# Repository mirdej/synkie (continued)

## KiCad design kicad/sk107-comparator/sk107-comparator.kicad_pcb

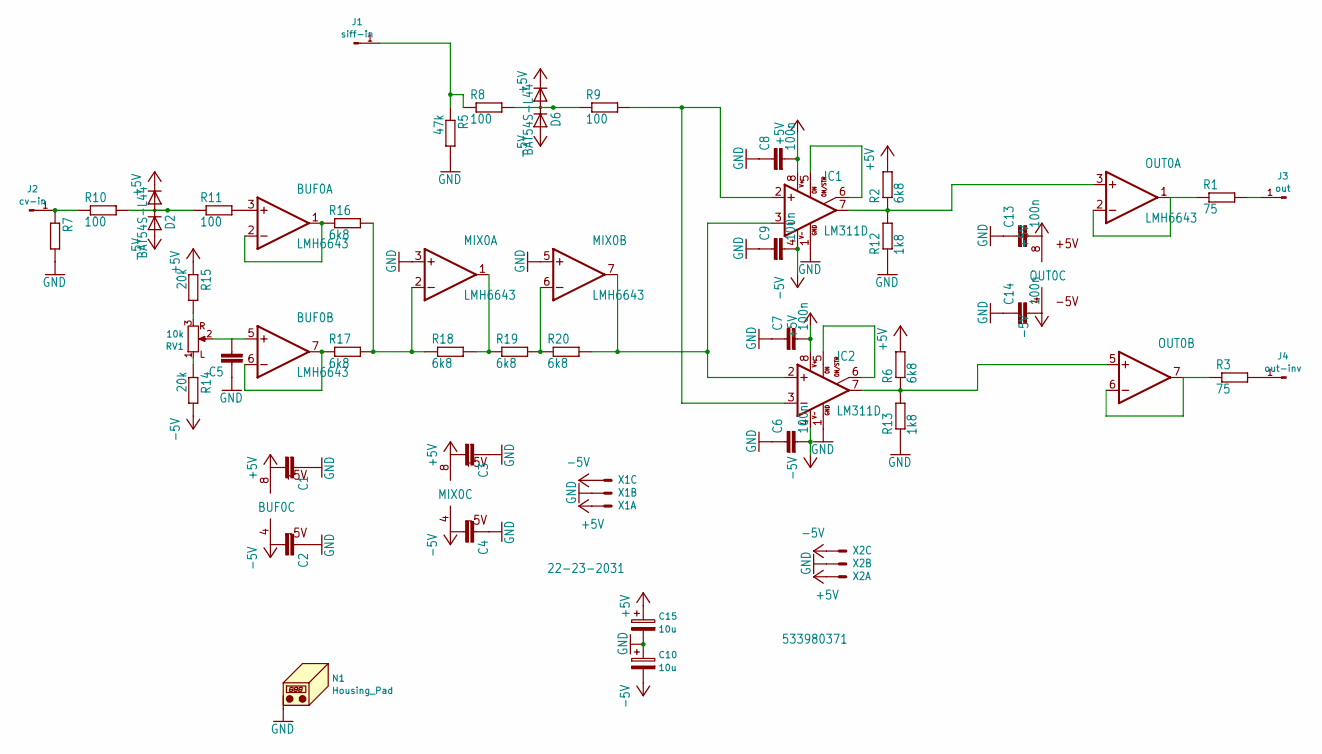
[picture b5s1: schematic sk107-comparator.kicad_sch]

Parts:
BUF0: LMH6643; VSSOP-8_3x3mm_P0.65mm; LCSC C478382
C1, C2, C3, C4, C5, C6, C7, C8, C9, C13, C14: 100n; C_0603_1608Metric_Pad1.05x0.95mm_HandSolder; LCSC C14663
C10, C15: 10u; C_1206_3216Metric_Pad1.42x1.75mm_HandSolder; LCSC C13585
D2, D6: BAT54S-L44; SOT-23; LCSC C8592
IC1, IC2: LM311D; SOIC-8_3.9x4.9mm_P1.27mm; LCSC C12597
J1: siff-in; Banana2mm-Löthülse
J2: cv-in; Banana2mm-Löthülse
J3: out; Banana2mm-Löthülse
J4: out-inv; Banana2mm-Löthülse
MIX0: LMH6643; VSSOP-8_3x3mm_P0.65mm; LCSC C478382
N1: Housing_Pad; Frontplate_20mm
OUT0: LMH6643; VSSOP-8_3x3mm_P0.65mm; LCSC C478382
R1, R3: 75; R_0603_1608Metric; LCSC C4275
R2, R6, R16, R17, R18, R19, R20: 6k8; R_0603_1608Metric; LCSC C23212
R5, R7: 47k; R_0603_1608Metric; LCSC C25819
R8, R9, R10, R11: 100; R_0603_1608Metric; LCSC C22775
R12, R13: 1k8; R_0603_1608Metric; LCSC C4177
R14, R15: 20k; R_0603_1608Metric; LCSC C4184
RV1: 10k; Alps_RK097_Frontplate
X1: 22-23-2031; Molex_KK-254_AE-6410-03A_1x03_P2.54mm_Vertical_SMD
X2: 533980371; Molex_PicoBlade_53398-0371_1x03-1MP_P1.25mm_Vertical; LCSC C293633

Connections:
+5V: BUF0.8 (+5V), C1.2, C3.2, C7.2, C8.2, C13.2, C15.1, D2.2 (C), D6.2 (C), IC1.8 (V+), IC2.8 (V+), MIX0.8 (+5V), OUT0.8 (+5V), R2.2, R6.2, R15.1, X1.1 (S), X2.1 (S)
-5V: BUF0.4 (-5V), C2.2, C4.2, C6.2, C9.2, C10.2, C14.2, D2.1 (A), D6.1 (A), IC1.4 (V-), IC2.4 (V-), MIX0.4 (-5V), OUT0.4 (-5V), R14.2, X1.3 (S), X2.3 (S)
GND: C1.1, C2.1, C3.1, C4.1, C5.1, C6.1, C7.1, C8.1, C9.1, C10.1, C13.1, C14.1, C15.2, IC1.1 (GND), IC2.1 (GND), MIX0.3 (+IN), MIX0.5 (+IN), N1.1 (PAD_1), R5.2, R7.2, R12.1, R13.1, X1.2 (S), X2.2 (S)
unnamed: BUF0.3 (+IN), R11.2
unnamed: BUF0.1 (OUT), BUF0.2 (-IN), R16.1
unnamed: BUF0.5 (+IN), C5.2, RV1.2
unnamed: BUF0.6 (-IN), BUF0.7 (OUT), R17.1
unnamed: D2.3 (AC), R10.2, R11.1
unnamed: D6.3 (AC), R8.2, R9.1
unnamed: IC1.2 (+IN), IC2.3 (-IN), R9.2
unnamed: IC1.3 (-IN), IC2.2 (+IN), MIX0.7 (OUT), R20.2
unnamed: IC1.5 (ON), IC1.6 (ON/STR)
unnamed: IC1.7 (OUT), OUT0.3 (+IN), R2.1, R12.2
unnamed: IC2.5 (ON), IC2.6 (ON/STR)
unnamed: IC2.7 (OUT), OUT0.5 (+IN), R6.1, R13.2
unnamed: J1.1 (Pin_1_1), R5.1, R8.1
unnamed: J2.1 (Pin_1_1), R7.1, R10.1
unnamed: J3.1 (Pin_1_1), R1.2
unnamed: J4.1 (Pin_1_1), R3.2
unnamed: MIX0.2 (-IN), R16.2, R17.2, R18.1
unnamed: MIX0.1 (OUT), R18.2, R19.1
unnamed: MIX0.6 (-IN), R19.2, R20.1
unnamed: OUT0.1 (OUT), OUT0.2 (-IN), R1.1
unnamed: OUT0.6 (-IN), OUT0.7 (OUT), R3.1
unnamed: R15.2, RV1.3
unnamed: R14.1, RV1.1 (L)

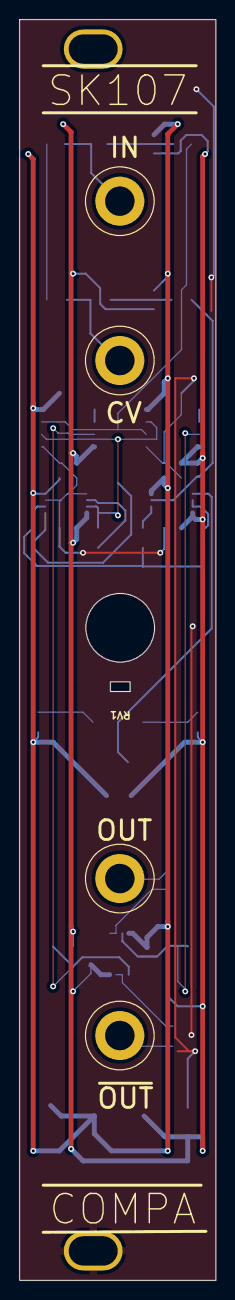
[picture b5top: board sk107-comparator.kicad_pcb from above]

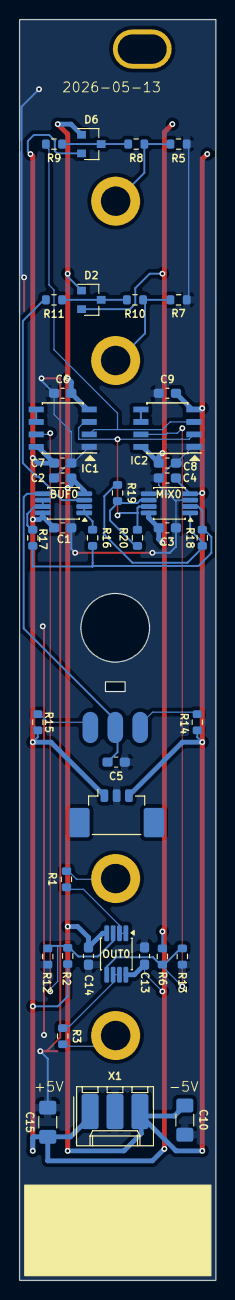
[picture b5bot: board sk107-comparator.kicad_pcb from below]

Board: 2 copper layers, 20.0 x 128.5 mm, 47 parts (41 on the bottom side), 26 nets.

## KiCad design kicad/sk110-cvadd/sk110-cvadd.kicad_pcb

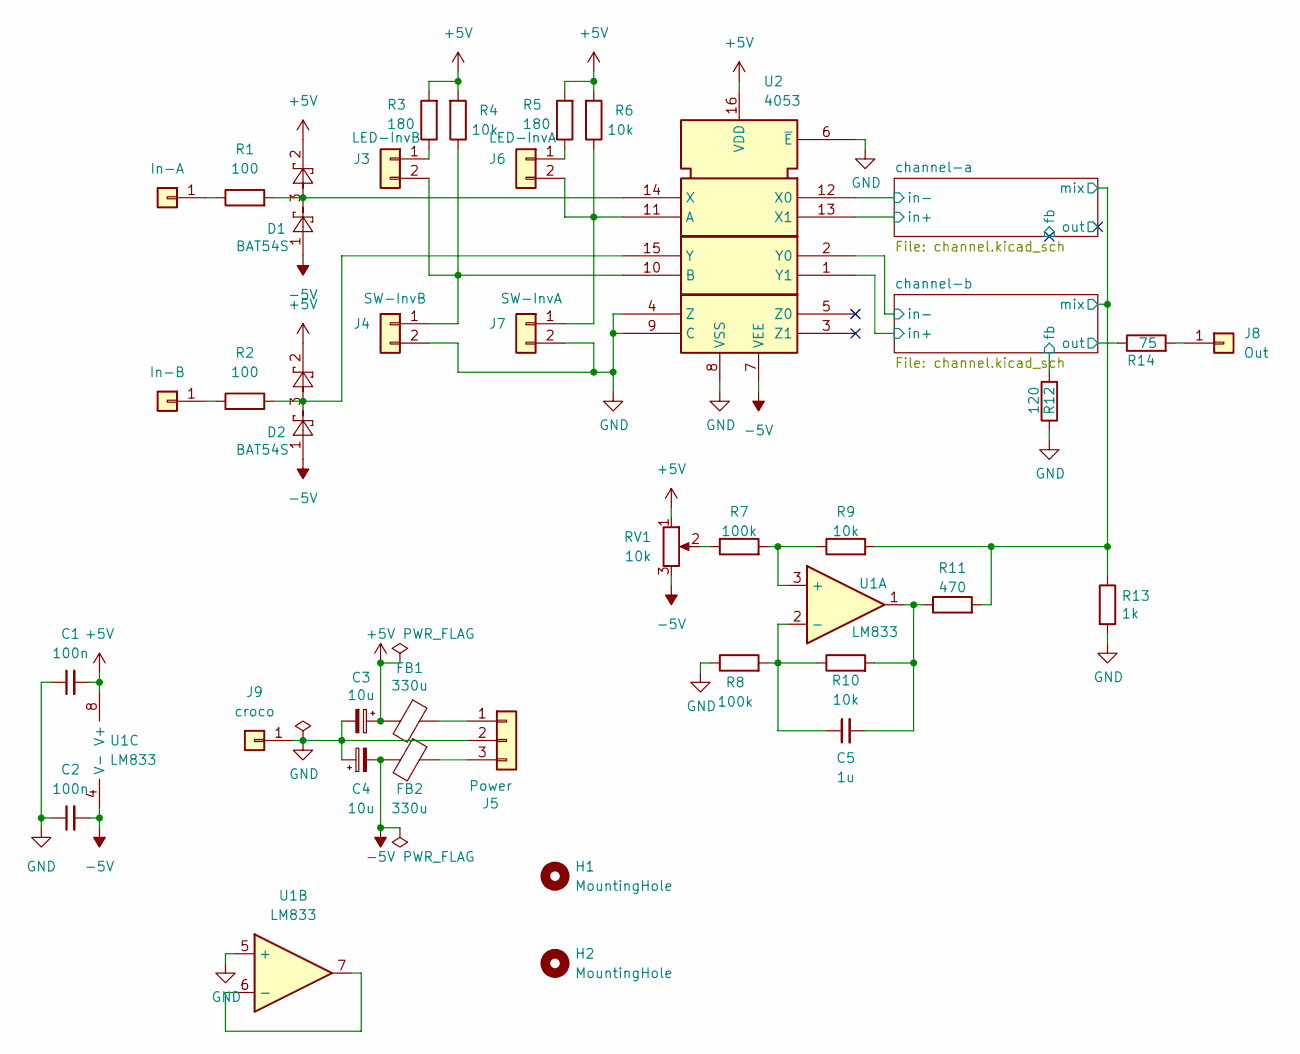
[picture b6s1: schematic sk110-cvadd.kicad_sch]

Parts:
C1, C2: 100n; C_0603_1608Metric_Pad1.05x0.95mm_HandSolder
C3, C4: 10u; C_0805_2012Metric_Pad1.15x1.40mm_HandSolder
C5: 1u; C_0603_1608Metric_Pad1.05x0.95mm_HandSolder
D1, D2: BAT54S; SOT-23
FB1, FB2: 330u; L_0805_2012Metric_Pad1.15x1.40mm_HandSolder
H1, H2: MountingHole; MountingHole_3.2mm_M3_DIN965
J1: In-A; Solderpad-SYNKIEPAD-2mm
J2: In-B; Solderpad-SYNKIEPAD-2mm
J3: LED-InvB; Molex_KK-254_AE-6410-02A_1x02_P2.54mm_Vertical
J4: SW-InvB; Molex_KK-254_AE-6410-02A_1x02_P2.54mm_Vertical
J5: Power; Molex_KK-254_AE-6410-03A_1x03_P2.54mm_Vertical
J6: LED-InvA; Molex_KK-254_AE-6410-02A_1x02_P2.54mm_Vertical
J7: SW-InvA; Molex_KK-254_AE-6410-02A_1x02_P2.54mm_Vertical
J8: Out; Solderpad-SYNKIEPAD-2mm
J9: croco; CrocodileGroundPad
R1, R2: 100; R_0805_2012Metric_Pad1.15x1.40mm_HandSolder
R3, R5: 180; R_0805_2012Metric_Pad1.15x1.40mm_HandSolder
R4, R6, R9, R10: 10k; R_0805_2012Metric_Pad1.15x1.40mm_HandSolder
R7, R8: 100k; R_0805_2012Metric_Pad1.15x1.40mm_HandSolder
R11: 470; R_0805_2012Metric_Pad1.15x1.40mm_HandSolder
R12: 120; R_0805_2012Metric_Pad1.15x1.40mm_HandSolder
R13: 1k; R_0805_2012Metric_Pad1.15x1.40mm_HandSolder
R14: 75; R_0805_2012Metric_Pad1.15x1.40mm_HandSolder
RV1: 10k; Potentiometer_Alps_RK09K_Single_Horizontal
U1: LM833; SOIC-8_3.9x4.9mm_P1.27mm
U2: 4053; SOIC-16_3.9x9.9mm_P1.27mm

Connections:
+5V: C1.2, C3.1, D1.2, D2.2, FB1.2, R3.2, R4.2, R5.2, R6.2, RV1.1, U1.8 (V+), U2.16 (VDD); also elsewhere on the board
-5V: C2.2, C4.2, D1.1, D2.1, FB2.2, RV1.3, U1.4 (V-), U2.7 (VEE); also elsewhere on the board
/channel-a/in+: U2.13 (X1); also elsewhere on the board
/channel-a/in-: U2.12 (X0); also elsewhere on the board
/channel-a/mix: R9.2, R11.2, R13.1; also elsewhere on the board
/channel-b/fb: R12.2; also elsewhere on the board
/channel-b/in+: U2.1 (Y1); also elsewhere on the board
/channel-b/in-: U2.2 (Y0); also elsewhere on the board
/channel-b/out: R14.1; also elsewhere on the board
GND: C1.1, C2.1, C3.2, C4.1, J4.2, J5.2, J7.2, J9.1, R8.1, R12.1, R13.2, U1.5 (+), U2.4 (Z), U2.6 (~E), U2.8 (VSS), U2.9 (C); also elsewhere on the board
unnamed: C5.2, R10.2, R11.1, U1.1
unnamed: J1.1, R1.1
unnamed: J2.1, R2.1
unnamed: J3.1, R3.1
unnamed: J3.2, J4.1, R4.1, U2.10 (B)
unnamed: FB1.1, J5.1
unnamed: FB2.1, J5.3
unnamed: J6.1, R5.1
unnamed: J6.2, J7.1, R6.1, U2.11 (A)
unnamed: J8.1, R14.2
unnamed: R7.1, RV1.2
unnamed: R7.2, R9.1, U1.3 (+)
unnamed: C5.1, R8.2, R10.1, U1.2 (-)
unnamed: U1.6 (-), U1.7
unnamed: D1.3, R1.2, U2.14 (X)
unnamed: D2.3, R2.2, U2.15 (Y)

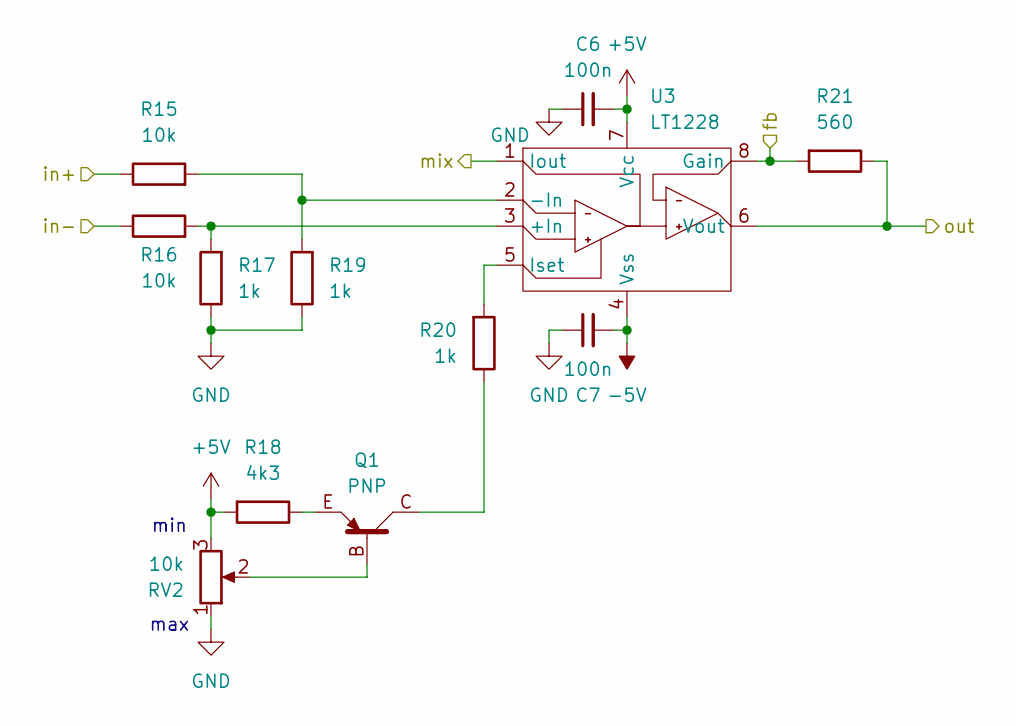
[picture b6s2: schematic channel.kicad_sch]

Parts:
C6, C7: 100n; C_0603_1608Metric_Pad1.05x0.95mm_HandSolder
Q1: PNP; SOT-23_BEC
R15, R16: 10k; R_0805_2012Metric_Pad1.15x1.40mm_HandSolder
R17, R19, R20: 1k; R_0805_2012Metric_Pad1.15x1.40mm_HandSolder
R18: 4k3; R_0805_2012Metric_Pad1.15x1.40mm_HandSolder
R21: 560; R_0805_2012Metric_Pad1.15x1.40mm_HandSolder
RV2: 10k; Potentiometer_Alps_RK09K_Single_Horizontal
U3: LT1228; SOIC-8_3.9x4.9mm_P1.27mm

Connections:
+5V: C6.2, R18.2, RV2.3, U3.7 (Vcc); also elsewhere on the board
-5V: C7.2, U3.4 (Vss); also elsewhere on the board
/channel-a/fb: R21.2, U3.8 (Gain)
/channel-a/in+: R15.1; also elsewhere on the board
/channel-a/in-: R16.1; also elsewhere on the board
/channel-a/mix: U3.1 (Iout); also elsewhere on the board
/channel-a/out: R21.1, U3.6 (Vout)
GND: C6.1, C7.1, R17.1, R19.1, RV2.1; also elsewhere on the board
unnamed: Q1.B, RV2.2
unnamed: Q1.C, R20.1
unnamed: Q1.E, R18.1
unnamed: R16.2, R17.2, U3.3 (+In)
unnamed: R15.2, R19.2, U3.2 (-In)
unnamed: R20.2, U3.5 (Iset)

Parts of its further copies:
C8, C9: 100n; C_0603_1608Metric_Pad1.05x0.95mm_HandSolder
Q2: PNP; SOT-23_BEC
R22, R23: 10k; R_0805_2012Metric_Pad1.15x1.40mm_HandSolder
R24, R26, R27: 1k; R_0805_2012Metric_Pad1.15x1.40mm_HandSolder
R25: 4k3; R_0805_2012Metric_Pad1.15x1.40mm_HandSolder
R28: 560; R_0805_2012Metric_Pad1.15x1.40mm_HandSolder
RV3: 10k; Potentiometer_Alps_RK09K_Single_Horizontal
U4: LT1228; SOIC-8_3.9x4.9mm_P1.27mm

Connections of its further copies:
+5V: C8.2, R25.2, RV3.3, U4.7 (Vcc); also elsewhere on the board
-5V: C9.2, U4.4 (Vss); also elsewhere on the board
/channel-a/mix: U4.1 (Iout); also elsewhere on the board
/channel-b/fb: R28.2, U4.8 (Gain); also elsewhere on the board
/channel-b/in+: R22.1; also elsewhere on the board
/channel-b/in-: R23.1; also elsewhere on the board
/channel-b/out: R28.1, U4.6 (Vout); also elsewhere on the board
GND: C8.1, C9.1, R24.1, R26.1, RV3.1; also elsewhere on the board
unnamed: Q2.B, RV3.2
unnamed: Q2.C, R27.1
unnamed: Q2.E, R25.1
unnamed: R23.2, R24.2, U4.3 (+In)
unnamed: R22.2, R26.2, U4.2 (-In)
unnamed: R27.2, U4.5 (Iset)

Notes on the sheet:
max
min

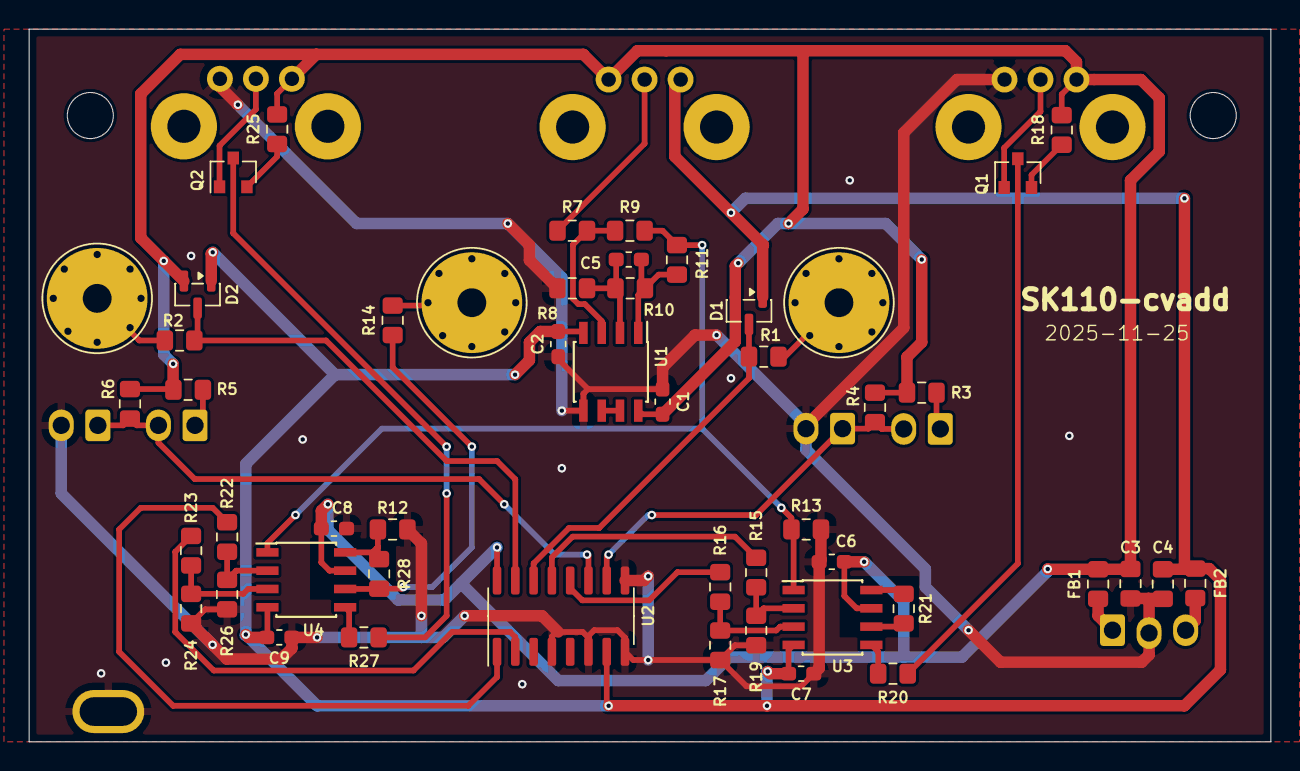
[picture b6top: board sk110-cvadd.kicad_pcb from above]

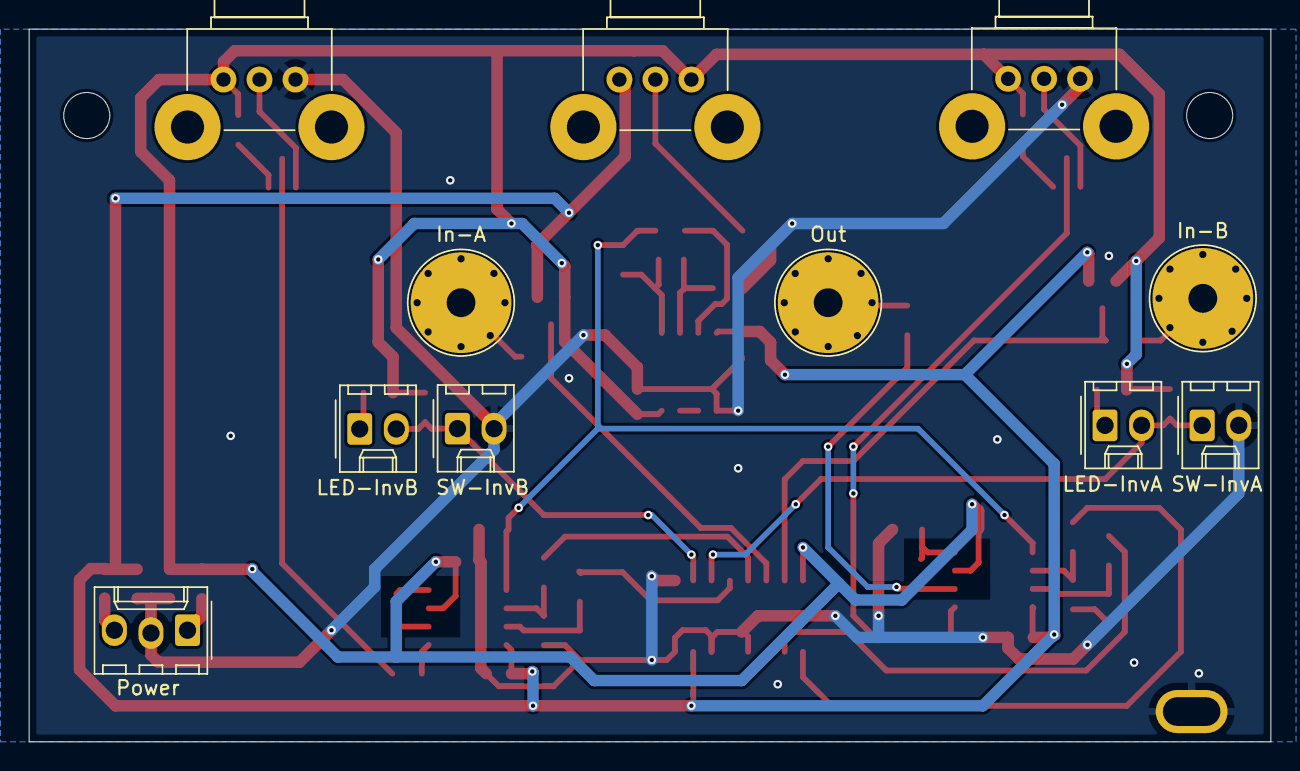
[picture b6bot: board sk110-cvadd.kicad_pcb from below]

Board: 2 copper layers, 86.2 x 49.5 mm, 61 parts (8 on the bottom side), 40 nets.

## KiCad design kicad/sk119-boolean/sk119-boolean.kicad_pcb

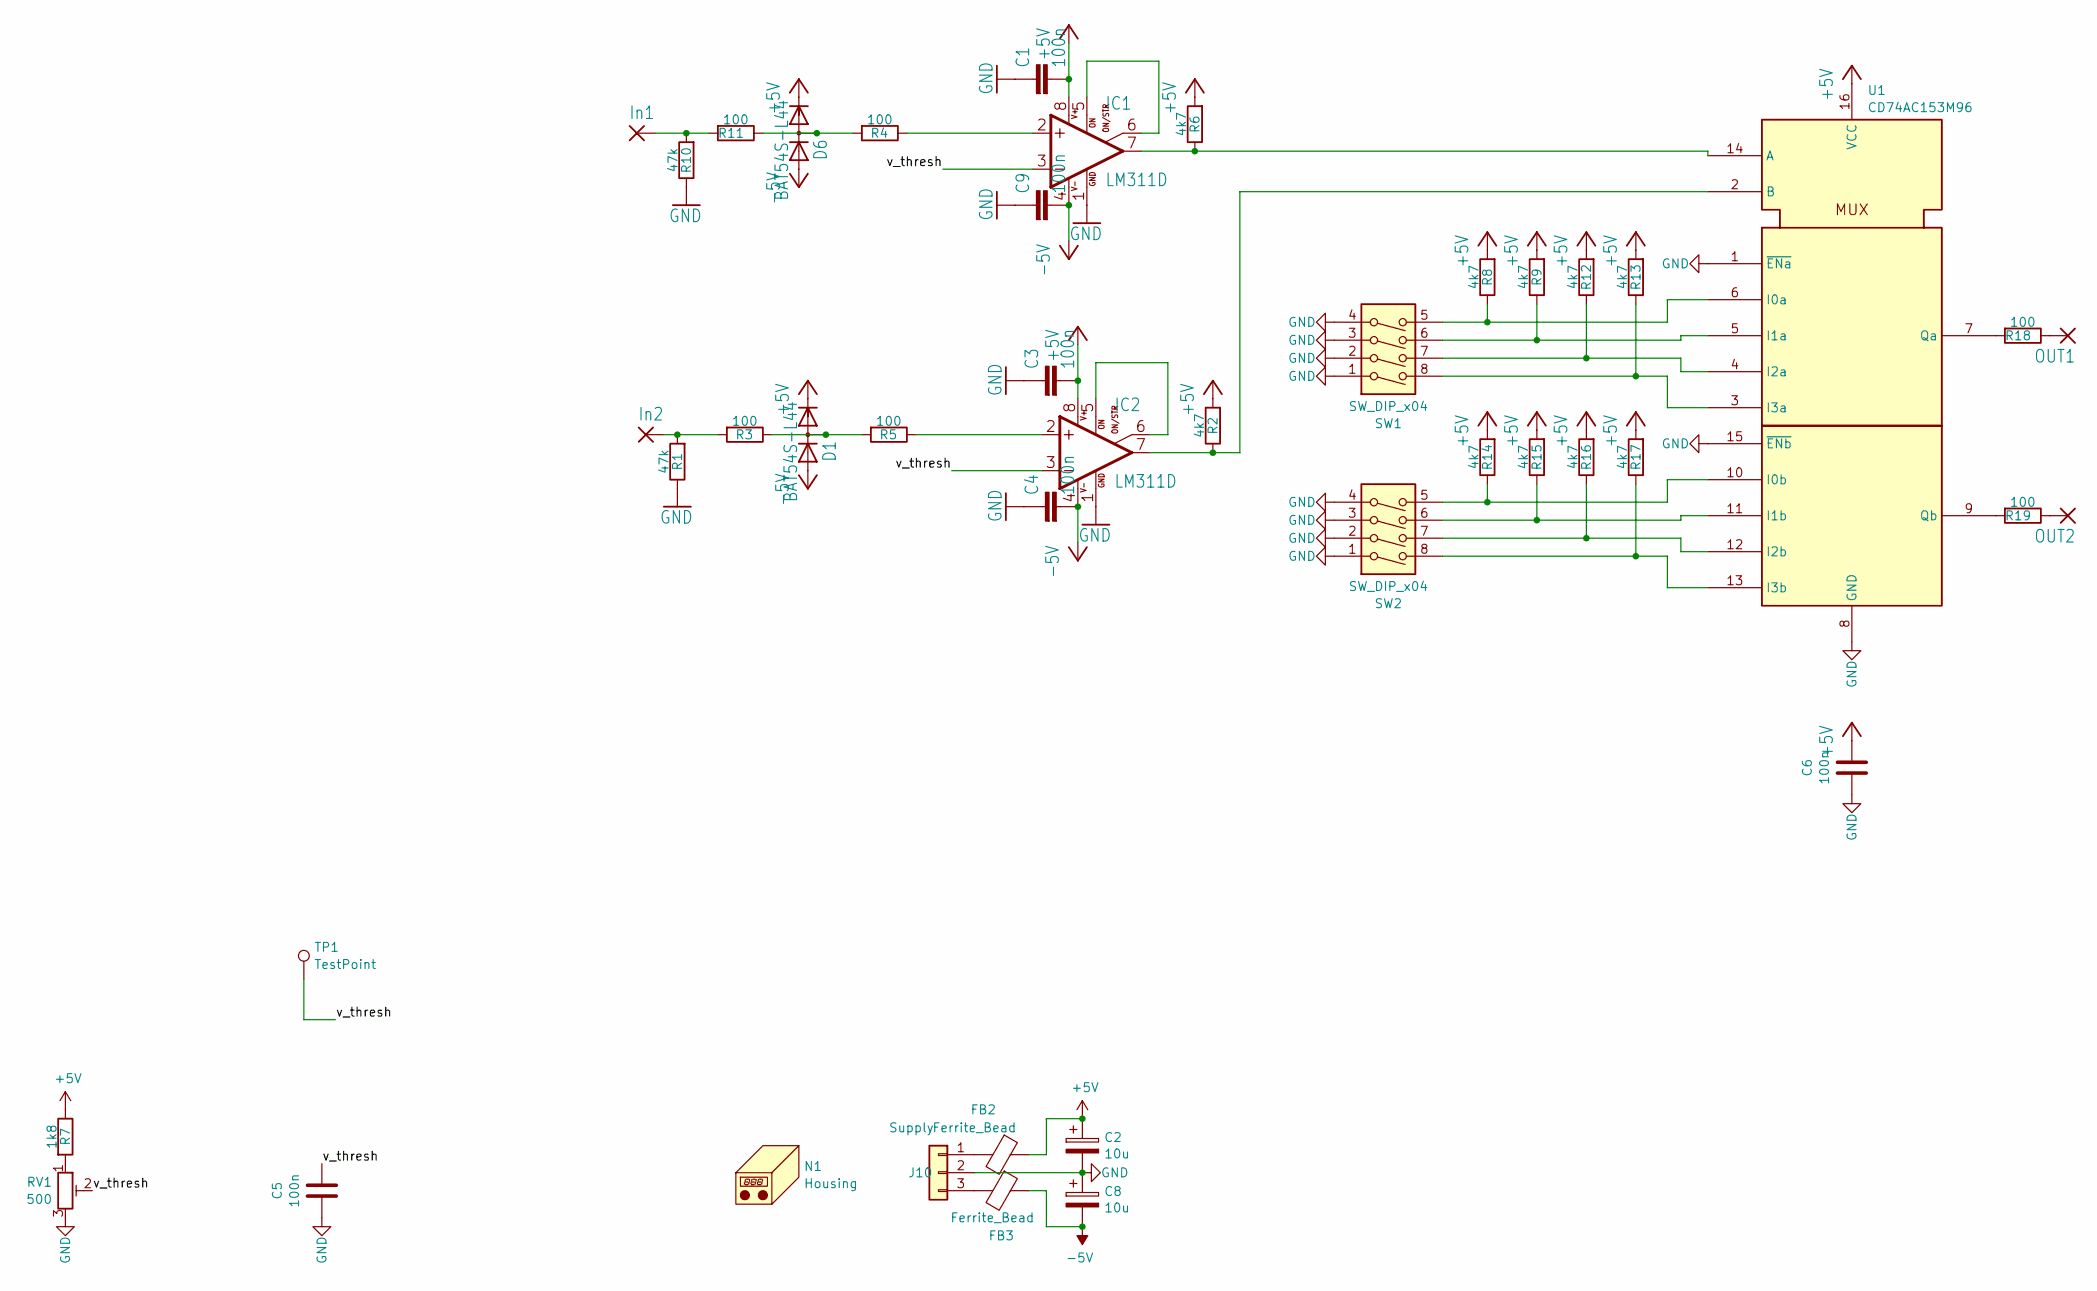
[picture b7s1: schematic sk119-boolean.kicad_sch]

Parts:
C1, C3, C4, C9: 100n; C_0603_1608Metric_Pad1.05x0.95mm_HandSolder; LCSC C14663
C2, C8: 10u; C_1206_3216Metric_Pad1.42x1.75mm_HandSolder; LCSC C13585
C5, C6: 100n; R_0603_1608Metric_Pad1.05x0.95mm_HandSolder; LCSC C14663
D1, D6: BAT54S-L44; SOT-23; LCSC C8592
FB2, FB3: Ferrite_Bead; L_0805_2012Metric_Pad1.05x1.20mm_HandSolder; LCSC C1017
IC1, IC2: LM311D; SOIC-8_3.9x4.9mm_P1.27mm; LCSC C12597
In1, In2: 3,17/1,1; Banana2mm-Löthülse
J10: Supply; smd-3pin
N1: Housing; Frontplate_20mm
OUT1, OUT2: 3,17/1,1; Banana2mm-Löthülse
R1, R10: 47k; R_0603_1608Metric; LCSC C25819
R2, R6, R8, R9, R12, R13, R14, R15, R16, R17: 4k7; R_0603_1608Metric; LCSC C23162
R3, R4, R5, R11, R18, R19: 100; R_0603_1608Metric; LCSC C22775
R7: 1k8; R_0603_1608Metric; LCSC C4177
RV1: 500; Potentiometer_Bourns_3314J_Vertical; LCSC C123873
SW1, SW2: SW_DIP_x04; CFS-0403TB-Bottom-Entry
TP1: TestPoint; TestPoint_Pad_D2.5mm
U1: CD74AC153M96; SOP-16_4.4x10.4mm_P1.27mm; LCSC C553188

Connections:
+5V: C1.2, C2.1, C3.2, C6.1, D1.2 (C), D6.2 (C), FB2.1, IC1.8 (V+), IC2.8 (V+), R2.2, R6.2, R7.1, R8.2, R9.2, R12.2, R13.2, R14.2, R15.2, R16.2, R17.2, U1.16 (VCC)
-5V: C4.2, C8.2, C9.2, D1.1 (A), D6.1 (A), FB3.1, IC1.4 (V-), IC2.4 (V-)
/v_thresh: C5.1, IC1.3 (-IN), IC2.3 (-IN), RV1.2, TP1.1
GND: C1.1, C2.2, C3.1, C4.1, C5.2, C6.2, C8.1, C9.1, IC1.1 (GND), IC2.1 (GND), J10.2, R1.1, R10.1, RV1.3, SW1.1, SW1.2, SW1.3, SW1.4, SW2.1, SW2.2, SW2.3, SW2.4, U1.1 (~ENa), U1.8 (GND), U1.15 (~ENb)
unnamed: D1.3 (AC), R3.1, R5.2
unnamed: D6.3 (AC), R4.2, R11.1
unnamed: IC1.2 (+IN), R4.1
unnamed: IC1.5 (ON), IC1.6 (ON/STR)
unnamed: IC1.7 (OUT), R6.1, U1.14 (A)
unnamed: IC2.2 (+IN), R5.1
unnamed: IC2.5 (ON), IC2.6 (ON/STR)
unnamed: IC2.7 (OUT), R2.1, U1.2 (B)
unnamed: In1.1, R10.2, R11.2
unnamed: In2.1, R1.2, R3.2
unnamed: FB2.2, J10.1
unnamed: FB3.2, J10.3
unnamed: OUT1.1, R18.1
unnamed: OUT2.1, R19.1
unnamed: R7.2, RV1.1
unnamed: R8.1, SW1.5, U1.6 (I0a)
unnamed: R14.1, SW2.5, U1.10 (I0b)
unnamed: R9.1, SW1.6, U1.5 (I1a)
unnamed: R15.1, SW2.6, U1.11 (I1b)
unnamed: R12.1, SW1.7, U1.4 (I2a)
unnamed: R16.1, SW2.7, U1.12 (I2b)
unnamed: R13.1, SW1.8, U1.3 (I3a)
unnamed: R17.1, SW2.8, U1.13 (I3b)
unnamed: R18.2, U1.7 (Qa)
unnamed: R19.2, U1.9 (Qb)

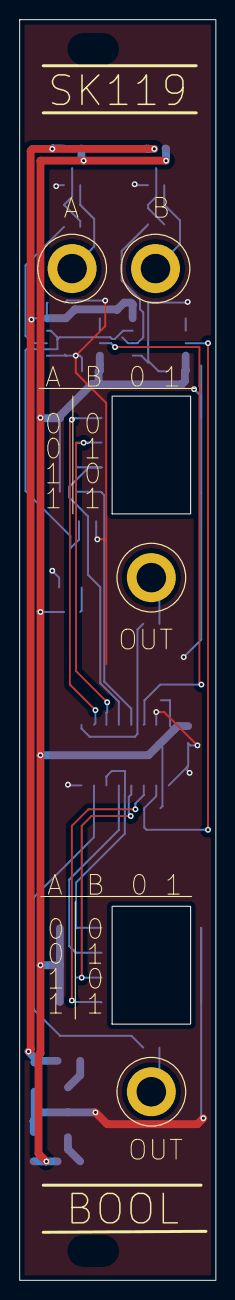
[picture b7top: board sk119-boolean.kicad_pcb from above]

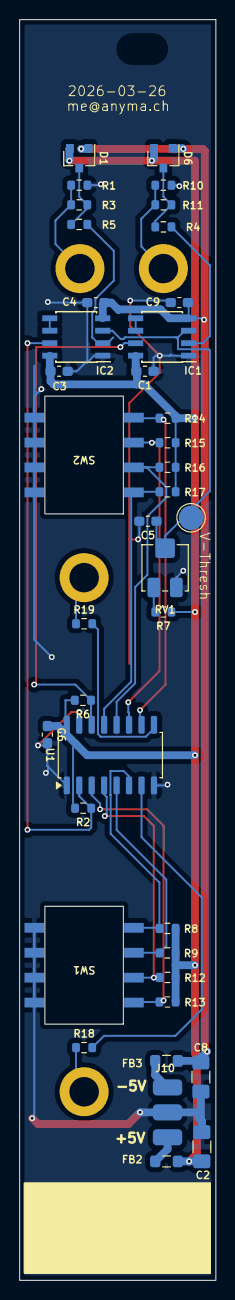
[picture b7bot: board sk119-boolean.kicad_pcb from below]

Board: 2 copper layers, 20.0 x 128.5 mm, 44 parts (39 on the bottom side), 29 nets.

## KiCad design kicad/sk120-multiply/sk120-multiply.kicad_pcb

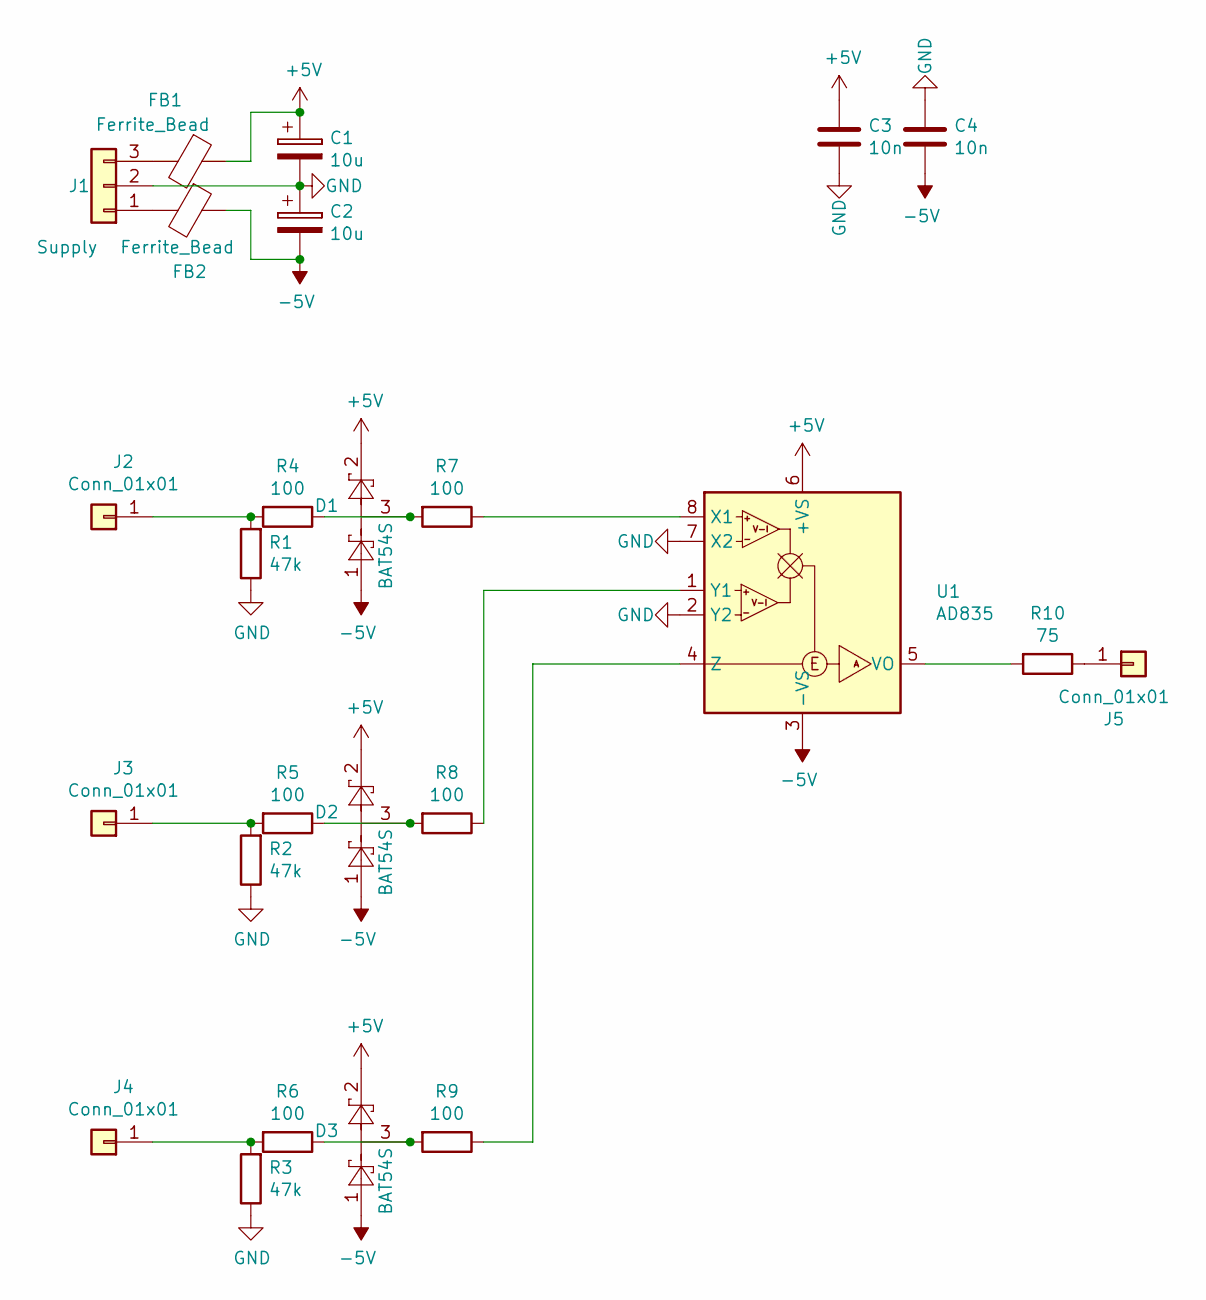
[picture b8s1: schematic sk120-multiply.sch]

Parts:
C1, C2: 10u; CP_EIA-3528-21_Kemet-B
C3, C4: 10n; C_1206_3216Metric_Pad1.42x1.75mm_HandSolder
D1, D2, D3: BAT54S; SOT-23
FB1, FB2: Ferrite_Bead; L_1206_3216Metric_Pad1.42x1.75mm_HandSolder
J1: Supply; Molex_KK-254_AE-6410-03A_1x03_P2.54mm_Vertical
J2, J3, J4, J5: Conn_01x01; Solderpad_1mm
R1, R2, R3: 47k; R_1206_3216Metric_Pad1.42x1.75mm_HandSolder
R4, R5, R6, R7, R8, R9: 100; R_1206_3216Metric_Pad1.42x1.75mm_HandSolder
R10: 75; R_1206_3216Metric_Pad1.42x1.75mm_HandSolder
U1: AD835; SOIC-8_3.9x4.9mm_P1.27mm

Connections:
+5V: C1.1, C3.1, D1.2, D2.2, D3.2, FB1.1, U1.6 (+VS)
-5V: C2.2, C4.2, D1.1, D2.1, D3.1, FB2.1, U1.3 (-VS)
GND: C1.2, C2.1, C3.2, C4.1, J1.2, R1.1, R2.1, R3.1, U1.2 (Y2), U1.7 (X2)
unnamed: D1.3, R4.1, R7.2
unnamed: D2.3, R5.1, R8.2
unnamed: D3.3, R6.1, R9.2
unnamed: FB1.2, J1.3
unnamed: FB2.2, J1.1
unnamed: J2.1, R1.2, R4.2
unnamed: J3.1, R2.2, R5.2
unnamed: J4.1, R3.2, R6.2
unnamed: J5.1, R10.1
unnamed: R7.1, U1.8 (X1)
unnamed: R8.1, U1.1 (Y1)
unnamed: R9.1, U1.4 (Z)
unnamed: R10.2, U1.5 (VO)

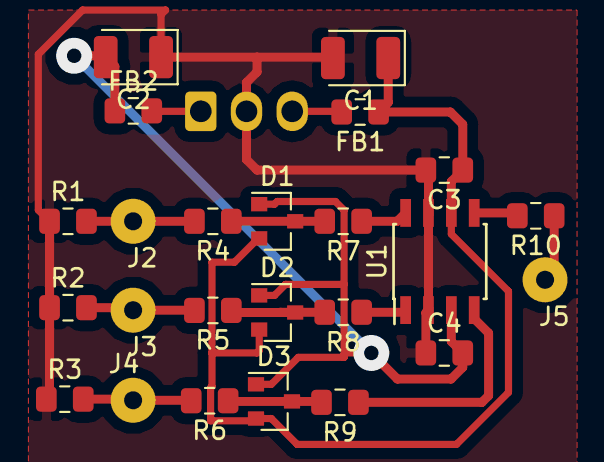
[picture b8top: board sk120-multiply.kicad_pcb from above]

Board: 2 copper layers, 25 parts (1 on the bottom side), 16 nets.
